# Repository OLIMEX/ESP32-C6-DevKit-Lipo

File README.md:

# MOD-ESP32-C6-DevKit-Lipo
ESP32-C6 WiFi6, Bluetooth 5 LE, Zigbee, Thread Matter breadboard friendly development board with Lipo charger and UEXT module

https://www.olimex.com/Products/IoT/ESP32-C6/ESP32-C6-DevKit-Lipo/

## Licensee
* Hardware is released under CERN Open Hardware Licence Version 2 - Strongly Reciprocal
* Software is released under MIT Licensee
* Documentation is released under CC BY-SA 4.0

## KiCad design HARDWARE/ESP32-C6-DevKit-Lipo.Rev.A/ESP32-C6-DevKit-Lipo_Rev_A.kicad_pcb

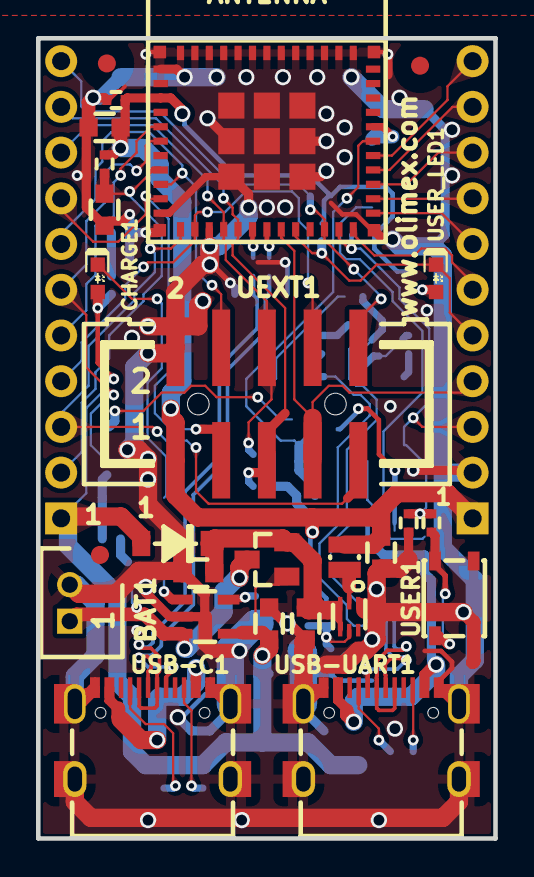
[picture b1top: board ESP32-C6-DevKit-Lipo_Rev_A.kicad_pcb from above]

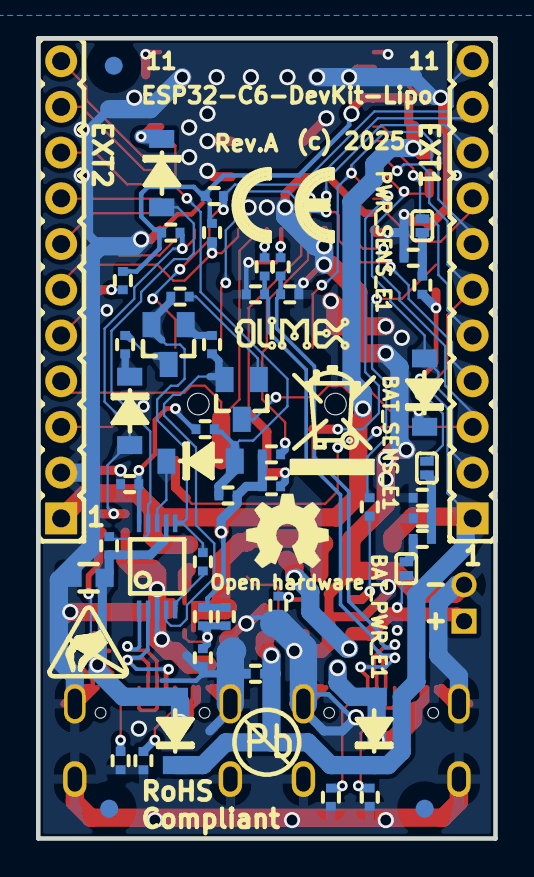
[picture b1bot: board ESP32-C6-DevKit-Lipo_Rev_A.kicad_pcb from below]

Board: 2 copper layers, 25.4 x 44.5 mm, 83 parts (57 on the bottom side), 59 nets.

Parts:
BAT1: DW02S; LIPO_BAT_VERTICAL_DW02S
BAT_PWR_E1: Opened; SJ_1_SMALLER
BAT_SENS_E1: Opened; SJ_1_SMALLER
C1, C7, C8, C11, C14: 22uF/6.3V/20%/X5R/C0603; C_0603_5MIL_DWS
C2, C4, C12: 100nF/10V/20%/X5R/C0402; C_0402_5MIL_DWS
C3: 1uF/10V/10%/X5R/C0603; C_0603_5MIL_DWS
C5, C6: 150pF/50V/2%/NP0/C0402; C_0402_5MIL_DWS
C9: NA(120pF/50V/5%/C0G/C0402); C_0402_5MIL_DWS
C10: NA(22uF/6.3V/20%/X5R/C0603); C_0603_5MIL_DWS
C13: NA(100nF/10V/20%/X5R/C0402); C_0402_5MIL_DWS
CHARGE1: LED/Yellow/0603; LED_0603_KA
D1, D2, D3, D4, D5, D6, D7: 1N5819S4(SOD-123); SOD-123_1C-2A_KA
EXT1, EXT2: HN1x11
FET1: IRLML6402TRPbF; SOT23
FID1, FID2, FID4, FID5: Fiducial; Fiducial1x3
FID3, FID6: Fiducial; Fiducial1x3_Paste
L1: 1.0uH/4.2A/DCR=35mR/20%/2.00x1.60x1.00mm/L2016(PI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; L_2016_MM
Logo_OLIMEX_80: Logo_OLIMEX_80
PWR_SENS_E1: Opened; SJ_1_SMALLER
Q1, Q2: BC817-40(SOT23); SOT23
R1: 220k/R0402; R_0402_5MIL_DWS
R2, R4, R9, R10, R18, R19: 10k/R0402; R_0402_5MIL_DWS
R3, R5, R6: 470k/R0402; R_0402_5MIL_DWS
R7, R8, R12, R21: 2.2k/R0402; R_0402_5MIL_DWS
R11, R20: NA(10k/R0402); R_0402_5MIL_DWS
R13, R14: 22R/R0402; R_0402_5MIL_DWS
R15: 180k/1%/R0402; R_0402_5MIL_DWS
R16: 10k/1%/R0402; R_0402_5MIL_DWS
R17: 40.2k/1%/R0402; R_0402_5MIL_DWS
R22, R28: 1k/R0402; R_0402_5MIL_DWS
R23: 4.7k/R0402; R_0402_5MIL_DWS
R24, R25, R26, R27: 5.1k/1%/R0402; R_0402_5MIL_DWS
R29: 100R/R0402; R_0402_5MIL_DWS
R30: 220R/R0402; R_0402_5MIL_DWS
Sign_Antistatic_Small: Sign_Antistatic; Sign_Antistatic_4.5mmX2.8mm
Sign_CE: CE_Sign
Sign_OSHW_7.3x6.0mm: Sign_OSHW_7.3x6.0mm; Sign_OSHW_7.3x6.0mmn
Sign_PB-Free: Sign_PB-Free
Sign_RecycleBin_1: Sign_RecycleBin_1
U1: ESP32-C6-MINI-1-N4
U2: TPS62A02ADRLR(SOT-563-6); SOT-563-6
U3: TP4054-42-SOT25-R; SOT-23-5
U4: CH340X(MSOP-10); MSOP-10_Pitch-0.5mm_3.00x3.00x1.00mm
UEXT1: P-B-V-10-LF; GBH-254-SMT-10
USB-C1: USB-C-16P-F(A40-00119-A52-12); USB2.0_TYPE-C(A40-00119-A52-12)_Paste
USB-UART1: USB-C-16P-F(A40-00119-A52-12); USB2.0_TYPE-C(A40-00119-A52-12)_Paste
USER1: YTS-A016-X
USER_LED1: LED/GREEN/0603; LED_0603_KA

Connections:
+3.3V: C1.1, C2.1, C8.1, C9.2, EXT2.1, L1.2, R2.1, R7.1, R8.1, R9.1, R10.1, R11.2, R15.2, R20.2, R21.1, U1.3 (3V3), UEXT1.1
+5V: C14.1, CHARGE1.2 (A), D1.2 (A), D2.1 (K), D3.1 (K), EXT1.1, FET1.1, R1.1, R4.1, U3.4 (VCC)
/D+: U4.1 (UD+), USB-UART1.A6 (DP1), USB-UART1.B6 (DP2)
/D-: U4.2 (UD-), USB-UART1.A7 (DN1), USB-UART1.B7 (DN2)
/ESP_EN: C3.1, D6.2 (A), EXT1.2, R2.2, U1.8 (EN)
/GPIO0/CLK: EXT1.3, U1.12 (IO0/GPIO0/XTAL_32K_P/LP_GPIO0/LP_UART_D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), UEXT1.9
/GPIO1/MOSI: EXT1.4, U1.13 (IO1/GPIO1/XTAL_32K_N/LP_GPIO1/LP_UART_D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), UEXT1.8
/GPIO2/EXT_POWER: EXT1.5, PWR_SENS_E1.2, U1.5 (IO2/GPIO2/LP_GPIO2/LP_UART_RTSN/ADC1_CH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)
/GPIO3/BAT_MEASURE: BAT_SENS_E1.2, EXT1.6, U1.6 (IO3/GPIO3/LP_GPIO3/LP_UART_CTSN/ADC1_CH3)
/GPIO4/LP_UART_RXD: EXT1.7, U1.9 (IO4/GPIO4/LP_GPIO4/LP_UART_RXD/MTMS/ADC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), UEXT1.4
/GPIO5/LP_UART_TXD: EXT1.8, U1.10 (IO5/GPIO5/LP_GPIO5/LP_UART_TXD/MTDI/ADC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), UEXT1.3
/GPIO6/LP_I2C_SDA: EXT1.9, R7.2, U1.15 (IO6/GPIO6/MTCK/LP_GPIO6/LP_I2C_SDA/ADC1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), UEXT1.6
/GPIO7/LP_I2C_SCL: EXT1.10, R8.2, U1.16 (IO7/GPIO7/MTDO/LP_GPIO7/LP_I2C_SCL/FSPID), UEXT1.5
/GPIO8/CS: EXT1.11, R9.2, U1.22 (IO8/GPIO8), UEXT1.10
/GPIO9/USER_BUT: C13.1, D7.2 (A), EXT2.3, R10.2, R29.1, U1.23 (IO9/GPIO9)
/GPIO14/MISO: EXT2.4, U1.19 (IO14/GPIO14), UEXT1.7
/GPIO15/USER_LED1: EXT2.5, R11.1, U1.20 (IO15/GPIO15), USER_LED1.1 (K)
/GPIO18: EXT2.6, U1.24 (IO18/GPIO18/SDIO_CMD/FSPICS2)
/GPIO19: EXT2.7, U1.25 (IO19/GPIO19/SDIO_CLK/FSPICS3)
/GPIO20: EXT2.8, U1.26 (IO20/GPIO20/SDIO_DATA0/FSPICS4)
/GPIO21: EXT2.9, U1.27 (IO21/GPIO21/SDIO_DATA1/FSPICS5)
/GPIO22: EXT2.10, U1.28 (IO22/GPIO22/SDIO_DATA2)
/GPIO23: EXT2.11, U1.29 (IO23/GPIO23/SDIO_DATA3)
/U0RXD: D4.2 (A), R19.2, R20.1, U1.30 (RXD0/U0RXD/GPIO17/FSPICS1)
/U0TXD: D5.1 (K), U1.31 (TXD0/U0TXD/GPIO16/FSPICS0)
/USB_D+: C5.1, R14.2, USB-C1.A6 (DP1), USB-C1.B6 (DP2)
/USB_D-: C6.1, R13.1, USB-C1.A7 (DN1), USB-C1.B7 (DN2)
GND: BAT1.2, C1.2, C2.2, C3.2, C4.1, C5.2, C6.2, C7.2, C8.2, C10.2, C11.2, C12.2, C13.2, C14.2, EXT2.2, R4.2, R5.2, R6.2, R16.1, R17.2, R24.1, R25.1, R26.1, R27.1, U1.1 (GND), U1.2 (GND), U1.11 (GND), U1.14 (GND), U1.36 (GND), U1.37 (GND), U1.38 (GND), U1.39 (GND), U1.40 (GND), U1.41 (GND), U1.42 (GND), U1.43 (GND), U1.44 (GND), U1.45 (GND), U1.46 (GND), U1.47 (GND), U1.48 (GND), U1.49 (GND), U1.50 (GND), U1.51 (GND), U1.52 (GND), U1.53 (GND), U2.1 (GND), U3.2 (GND), U4.3 (GND), UEXT1.2, USB-C1.0 (SHELL), USB-C1.A1 (GND), USB-C1.A12 (GND), USB-C1.B1 (GND), USB-C1.B12 (GND), USB-UART1.0 (SHELL), USB-UART1.A1 (GND), USB-UART1.A12 (GND), USB-UART1.B1 (GND), USB-UART1.B12 (GND), USER1.1
unnamed: BAT_PWR_E1.1, R3.1
unnamed: BAT_SENS_E1.1, C4.2, R3.2, R6.1
unnamed: CHARGE1.1 (K), R12.2
unnamed: C7.1, C10.1, D1.1 (K), FET1.2, U2.3 (VIN), U2.4 (EN)
unnamed: C11.1, D2.2 (A), R18.1, U4.7 (VCC), USB-UART1.A4 (VBUS), USB-UART1.A9 (VBUS), USB-UART1.B4 (VBUS), USB-UART1.B9 (VBUS)
unnamed: D3.2 (A), USB-C1.A4 (VBUS), USB-C1.A9 (VBUS), USB-C1.B4 (VBUS), USB-C1.B9 (VBUS)
unnamed: D4.1 (K), U4.8 (TXD)
unnamed: D5.2 (A), R18.2, U4.9 (RXD)
unnamed: D6.1 (K), Q1.3 (C)
unnamed: D7.1 (K), R30.2
unnamed: PWR_SENS_E1.1, R1.2, R5.1
unnamed: Q1.1 (B), R22.2
unnamed: Q1.2 (E), R28.1, U4.4 (RTS#)
unnamed: Q2.1 (B), R28.2
unnamed: Q2.3 (C), R30.1
unnamed: Q2.2 (E), R22.1, R23.1, U4.6 (TNOW/DTR#)
unnamed: R29.2, USER1.2
unnamed: R13.2, U1.17 (IO12/GPIO12/USB_D-)
unnamed: R14.1, U1.18 (IO13/GPIO13/USB_D+)
unnamed: C9.1, R15.1, R17.1, U2.5 (FB)
unnamed: L1.1, U2.2 (SW)
unnamed: R12.1, U3.1 (CHRGb)
unnamed: R16.2, U3.5 (PROG)
unnamed: R23.2, U4.5 (CTS#)
unnamed: C12.1, R19.1, U4.10 (V3)
unnamed: R27.2, USB-C1.A5 (CC1)
unnamed: R26.2, USB-C1.B5 (CC2)
unnamed: R25.2, USB-UART1.A5 (CC1)
unnamed: R24.2, USB-UART1.B5 (CC2)
unnamed: R21.2, USER_LED1.2 (A)
VBAT: BAT1.1, BAT_PWR_E1.2, FET1.3, U3.3 (VBAT)

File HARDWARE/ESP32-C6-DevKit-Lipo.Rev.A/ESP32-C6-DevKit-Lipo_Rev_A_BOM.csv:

"Id";"Designator";"Footprint";"Quantity";"Designation";"Supplier and ref";
1;"USB-C1,USB-UART1";"USB2.0_TYPE-C(A40-00119-A52-12)_Paste";2;"USB-C-16P-F(A40-00119-A52-12)";;;
2;"CHARGE1";"LED_0603_KA";1;"LED/Yellow/0603";;;
3;"C14,C8,C1,C7,C11";"C_0603_5MIL_DWS";5;"22uF/6.3V/20%/X5R/C0603";;;
4;"FID3,FID6";"Fiducial1x3_Paste";2;"Fiducial";;;
5;"C2,C13,C4,C12";"C_0402_5MIL_DWS";4;"100nF/10V/20%/X5R/C0402";;;
6;"C3";"C_0603_5MIL_DWS";1;"1uF/10V/10%/X5R/C0603";;;
7;"USER_LED1";"LED_0603_KA";1;"LED/GREEN/0603";;;
8;"U2";"SOT-563-6";1;"TPS62A02ADRLR(SOT-563-6)";;;
9;"R29";"R_0402_5MIL_DWS";1;"100R/R0402";;;
10;"UEXT1";"GBH-254-SMT-10";1;"P-B-V-10-LF";;;
11;"U1";"ESP32-C6-MINI-1-N4";1;"ESP32-C6-MINI-1-N4";;;
12;"R2,R19,R18,R4,R9,R10";"R_0402_5MIL_DWS";6;"10k/R0402";;;
13;"U3";"SOT-23-5";1;"TP4054-42-SOT25-R";;;
14;"FID1,FID2,FID4,FID5";"Fiducial1x3";4;"Fiducial";;;
15;"D1,D5,D2,D7,D3,D4,D6";"SOD-123_1C-2A_KA";7;"1N5819S4(SOD-123)";;;
16;"FET1";"SOT23";1;"WPM2015-3/TR";;;
17;"BAT1";"LIPO_BAT_VERTICAL_DW02S";1;"DW02S";;;
18;"L1";"L_2016_MM";1;"1.0uH/4.2A/DCR=35mR/20%/2.00x1.60x1.00mm/L2016(PIM201610-1R0MTS00)";;;
19;"C10";"C_0603_5MIL_DWS";1;"NA(22uF/6.3V/20%/X5R/C0603)";;;
20;"USER1";"YTS-A016-X";1;"YTS-A016-X";;;
21;"C5,C6";"C_0402_5MIL_DWS";2;"150pF/50V/2%/NP0/C0402";;;
22;"Q1,Q2";"SOT23";2;"BC817-40(SOT23)";;;
23;"R17";"R_0402_5MIL_DWS";1;"40.2k/1%/R0402";;;
24;"R27,R26,R25,R24";"R_0402_5MIL_DWS";4;"5.1k/1%/R0402";;;
25;"R22,R28";"R_0402_5MIL_DWS";2;"1k/R0402";;;
26;"PWR_SENS_E1,BAT_PWR_E1,BAT_SENS_E1";"SJ_1_SMALLER";3;"Opened";;;
27;"R3,R5,R6";"R_0402_5MIL_DWS";3;"470k/R0402";;;
28;"R23";"R_0402_5MIL_DWS";1;"4.7k/R0402";;;
29;"C9";"C_0402_5MIL_DWS";1;"NA(120pF/50V/5%/C0G/C0402)";;;
30;"R16";"R_0402_5MIL_DWS";1;"10k/1%/R0402";;;
31;"R15";"R_0402_5MIL_DWS";1;"180k/1%/R0402";;;
32;"EXT1,EXT2";"HN1x11";2;"HN1x11";;;
33;"U4";"MSOP-10_Pitch-0.5mm_3.00x3.00x1.00mm";1;"CH340X(MSOP-10)";;;
34;"R20,R11";"R_0402_5MIL_DWS";2;"NA(10k/R0402)";;;
35;"R7,R12,R21,R8";"R_0402_5MIL_DWS";4;"2.2k/R0402";;;
36;"R30";"R_0402_5MIL_DWS";1;"220R/R0402";;;
37;"R13,R14";"R_0402_5MIL_DWS";2;"22R/R0402";;;
38;"R1";"R_0402_5MIL_DWS";1;"220k/R0402";;;

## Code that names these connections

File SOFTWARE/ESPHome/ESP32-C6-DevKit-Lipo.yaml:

esphome:
  name: esp32-c6-devkit-lipo
  friendly_name: ESP32-C6-DevKit-Lipo

esp32:
  board: esp32-c6-devkitc-1
  variant: esp32c6
  framework:
    type: arduino

# ============================================================
# LOGGING / CONTROL
# ============================================================
logger:
api:
ota:
captive_portal:

wifi:
  ssid: "YOUR_SSID"
  password: "YOUR_PASSWORD"
  ap:
    ssid: "ESP32-C6-DevKit-Lipo Fallback"
    password: "12345678"

# ============================================================
# 🔴 USER LED — GPIO15
# ============================================================
output:
  - platform: gpio
    pin: GPIO15
    id: user_led_output

light:
  - platform: binary
    name: "ESP32-C6-DevKit-Lipo User LED"
    output: user_led_output

# ============================================================
# 🔘 USER BUTTON — GPIO9
# ============================================================
binary_sensor:
  - platform: gpio
    name: "ESP32-C6-DevKit-Lipo User Button"
    pin:
      number: GPIO9
      mode:
        input: true
        pullup: true
      inverted: true
    on_press:
      - light.toggle: user_led_output

# ============================================================
# 🔌 UEXT I2C — GPIO7 SCL / GPIO6 SDA
# ============================================================
i2c:
  sda: GPIO6
  scl: GPIO7
  scan: true

# ============================================================
# 🔌 UEXT SPI BUS
# ============================================================
spi:
  clk_pin: GPIO0
  mosi_pin: GPIO1
  miso_pin: GPIO14

# Chip Select pin available for devices:
# GPIO8

# ============================================================
# 🔌 UEXT UART — GPIO5 TX / GPIO4 RX
# ============================================================
uart:
  - id: uext_uart
    tx_pin: GPIO5
    rx_pin: GPIO4
    baud_rate: 115200

# ============================================================
# 🔋 BATTERY VOLTAGE — GPIO3 (jumpers must be closed)
# Divider: 470k / 470k → ×2 scaling
# ============================================================
sensor:
  - platform: adc
    pin: GPIO3
    name: "ESP32-C6-DevKit-Lipo Battery Voltage"
    attenuation: 11db
    update_interval: 30s
    filters:
      - multiply: 2.0
    unit_of_measurement: "V"
    accuracy_decimals: 2
    device_class: voltage
    state_class: measurement

# ============================================================
# 🔌 EXTERNAL POWER SENSE — GPIO2 (jumpers required)
# ============================================================
binary_sensor:
  - platform: gpio
    name: "ESP32-C6-DevKit-Lipo External Power"
    pin:
      number: GPIO2
      mode: input

# ============================================================
# HARDWARE NOTES — ESP32-C6-DevKit-Lipo
# ============================================================
# CH340 USB-UART uses GPIO16 (TX) and GPIO17 (RX)
# Avoid using these pins if programming over that port.
#
# GPIO0, GPIO8 are boot-related + SPI — keep stable at boot.
# No PSRAM on ESP32-C6-MINI-1-N4.
# ADC range is 0–3.3V only.

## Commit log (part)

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2025-12-05 initial upload
2025-12-05 add user manual
2026-02-11 Update
    Added PlatformIO and ESPHome configs

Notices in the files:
HARDWARE/ESP32-C6-DevKit-Lipo.Rev.A/ESP32-C6-DevKit-Lipo_Rev_A.kicad_pcb:
(c) 2025
